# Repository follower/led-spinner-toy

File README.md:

# LED Spinner Toy

Flashy LED toy designed with KiCad

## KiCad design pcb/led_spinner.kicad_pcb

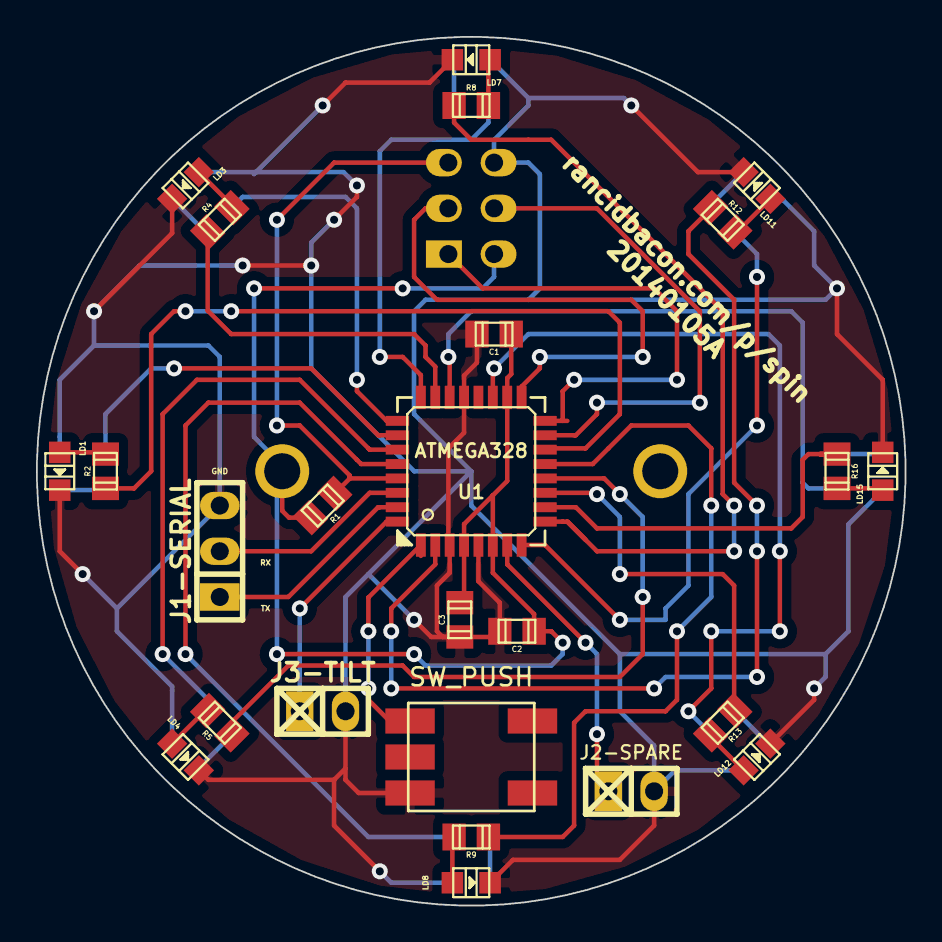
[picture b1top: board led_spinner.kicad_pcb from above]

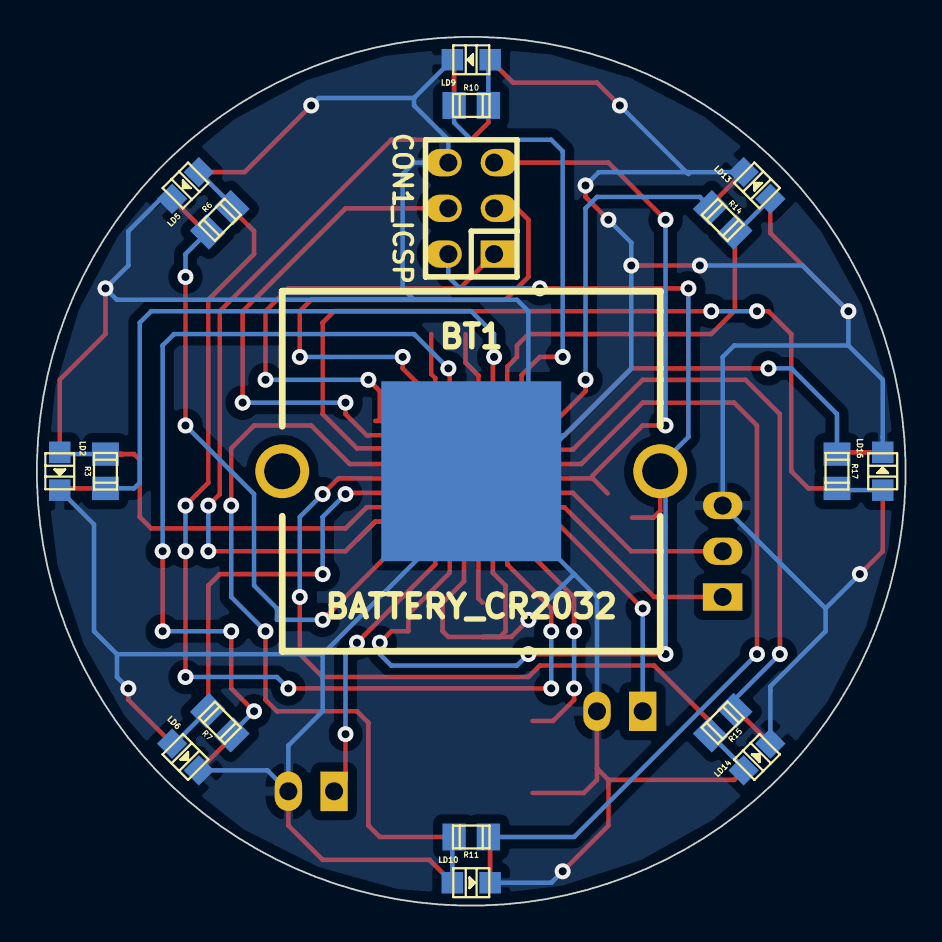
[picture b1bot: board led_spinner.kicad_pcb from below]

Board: 2 copper layers, 48.3 x 48.3 mm, 43 parts (18 on the bottom side), 43 nets.

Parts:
BT1: BATTERY_CR2032; CR2032_HOLDER_KEYSTONE_3003
C1, C2, C3: C; c_0805
CON1_ICSP: AVR-ISP-6; pin_socket_3x2
J1-SERIAL: SERIAL; pin_socket_3
J2-SPARE: SPARE; pin_socket_2
J3-TILT: TILT; pin_socket_2
LD1, LD2, LD3, LD4, LD5, LD6, LD7, LD8, LD9, LD10, LD11, LD12, LD13, LD14, LD15, LD16: LED; Led_0805
R1, R2, R3, R4, R5, R6, R7, R8, R9, R10, R11, R12, R13, R14, R15, R16, R17: R; r_0805
SW1: SW_PUSH; OMRON-PUSH-BUTTON-B3SN-3112P
U1: ATMEGA328; lqfp32

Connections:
+BATT: BT1.0, C1.2, C2.2, C3.1, CON1_ICSP.2, R1.1, U1.4, U1.6, U1.18
/BE: R17.2, U1.26
/BN: R10.2, U1.24
/BNE: R14.2, U1.25
/BNW: R6.2, U1.8
/BS: R11.2, U1.28
/BSE: R15.2, U1.27
/BSW: R7.2, U1.19
/BUTTON: SW1.1, U1.1
/BW: R3.2, U1.22
/FE: R16.2, U1.10
/FN: R8.2, U1.9
/FNE: R12.2, U1.2
/FNW: R4.2, U1.23
/FS: R9.2, U1.13
/FSE: R13.2, U1.11
/FSW: R5.2, U1.12
/FW: R2.2, U1.14
/MISO: CON1_ICSP.1, U1.16
/MOSI: CON1_ICSP.4, U1.15
/RXD: J1-SERIAL.2, U1.30
/SCK: CON1_ICSP.3, U1.17
/TXD: J1-SERIAL.1, U1.31
/~RESET: CON1_ICSP.5, R1.2, U1.29
GND: BT1.2, C1.1, C2.1, C3.2, CON1_ICSP.6, J1-SERIAL.3, J2-SPARE.2, J3-TILT.2, LD1.2, LD2.2, LD3.2, LD4.2, LD5.2, LD6.2, LD7.2, LD8.2, LD9.2, LD10.2, LD11.2, LD12.2, LD13.2, LD14.2, LD15.2, LD16.2, SW1.3, U1.3, U1.5, U1.21
unnamed: J2-SPARE.1, U1.7
unnamed: J3-TILT.1, U1.32
unnamed: LD1.1, R2.1
unnamed: LD2.1, R3.1
unnamed: LD3.1, R4.1
unnamed: LD4.1, R5.1
unnamed: LD5.1, R6.1
unnamed: LD6.1, R7.1
unnamed: LD7.1, R8.1
unnamed: LD8.1, R9.1
unnamed: LD9.1, R10.1
unnamed: LD10.1, R11.1
unnamed: LD11.1, R12.1
unnamed: LD12.1, R13.1
unnamed: LD13.1, R14.1
unnamed: LD14.1, R15.1
unnamed: LD15.1, R16.1
unnamed: LD16.1, R17.1

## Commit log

2013-12-22 Add default KiCad project file.
2013-12-22 Remove standard libraries.
2013-12-22 Import and include library <http://smisioto.no-ip.org/kicad_libs/library/lib_w_microcontrollers.zip> version (30/11/2013).
2013-12-22 Add default schematic file.
2013-12-24 Add ATmega328 to schematic.
2013-12-24 Move PCB related files into a subdirectory for better organisation.
2013-12-24 Add poor README.
2013-12-24 Import KiCad power library from <https://github.com/KiCad/kicad-library/raw/af0f01971809334bbfe6d6f22faec33e7056694c/library/power.lib>.
2013-12-24 Use KiCad power library.
2013-12-24 Add power flags required by KiCad.
2013-12-24 Move the MCU symbol so it's grid aligned.
2013-12-24 Add power and ground connections to MCU.
2013-12-24 Annotate the symbols.
2013-12-24 Import discrete device/components library from <http://smisioto.no-ip.org/kicad_libs/library/lib_w_device.zip> version (22/06/2013).
2013-12-24 Include previously imported library.
2013-12-24 Add imported library to schematic file also (not sure why this didn't happen before).
2013-12-24 Add decoupling caps.
2013-12-24 Add reset pull-up.
2013-12-24 Add TODO list to schematic.
2013-12-26 Import version of `atmel.lib` from <https://raw.github.com/KiCad/kicad-library/ed1b4733563014e8e1b31147cb90239def444825/library/atmel.lib> so we can use the AVR-ISP-6 schematic symbol. [Note: It's LG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
2013-12-26 Add imported library to project.
2013-12-26 Add ISP connector section.
2013-12-26 Add my CR2032 battery symbol (with the 3 pin workaround).
2013-12-26 Add CR2032 battery section to schematic.
2013-12-26 Add front & back side LEDs with appropriate PWM connections where required.
2013-12-26 Make AREF non-connected.
2013-12-26 Import and include connectors library from <http://smisioto.no-ip.org/kicad_libs/library/lib_w_connectors.zip> (version 12/10/2013).
2013-12-26 Add serial connector (not particularly standard).
2013-12-26 Add a connection point for a currently unused pin.
2013-12-26 Change the spare connection to have a ground connection too which probably makes it more useful--if we can fit it physically.
2013-12-26 Add connection point for tilt sensor.
2013-12-26 Rename unnamed connectors to indicate their use.
2013-12-26 Add the alternate pinout push button that I originally created for the reaction tester game project from the <http://smisioto.no-ip.org/> device library.
2013-12-26 Add button section.
2013-12-27 Add my custom footprints for push button switch and CR2032 battery retainer from reaction tester game repository.
2013-12-27 Import multiple footprints from <http://smisioto.no-ip.org/elettronica/kicad/kicad-en.htm>.
2013-12-27 Add generated net list.
2013-12-27 Remove default footprint library links.
2013-12-27 Remove alias thingy.
2013-12-27 Include libraries in project.
2013-12-27 KiCad automatic config change shenanigans.
2013-12-27 Add default component to footprint mapping file.
2013-12-27 Add "new style" library table with the libraries. Map components to footprints.
2013-12-27 Add default "blank" pcb layout.
2013-12-27 Add board outline to pcb. Add modules with rough (relative) positioning.
2013-12-27 Move four N,E,S,W front LEDs into correct place (based on current board size).
2013-12-27 Move all back side LEDs to the back of the board.
2013-12-27 Move front NE,SE,SW,NW LEDs into position. The positions aren't entirely perfect due to interaction between the 45 degree angle and the forced snap to grid.
2013-12-27 Fix LED/resistor pairs that didn't have the correct ends together.
2013-12-27 Add tracks between LED and resistors.
2013-12-27 Lay tracks to decoupling caps, reset pull up resistor and signal connections to all front LEDs.
2013-12-30 Route signals to back-side LEDs. Route signals to connectors except for ICSP. Route button.
2013-12-30 Remove some extra overlapping track segments.
2013-12-30 Route ICSP header. Route battery connections.
2013-12-30 Route ground connections in preparation for ground planes.
2013-12-30 Route one missed ground connection.
2013-12-30 Add ground zone on the front and back.
2013-12-30 Fix two DRC errors. The microcontroller pads are too close together according to the default rule so change the clearance for just that to 6 mil. There was one track too close to a SMD pad so fixed t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
2014-01-05 Tidy up the front silkscreen. (Remove off-board silkscreen. Remove overlaps. Add useful connector names.)
2014-01-05 Fix up back silkscreen.
2014-01-05 Add project and version ID text.
2014-01-05 Change PCB gerber export settings.
2014-01-05 Add exported Gerbers used to send to PCB manufacturer.
2014-11-05 Add the second initial revision of "half" of the enclosure.
2014-11-05 Add initial back part of enclosure. (Seems to be a little to thin to print well and also the inner edge isn't quite close enough to seal well.)
2014-11-05 Quick commit of sample code currently used for demo. Very power inefficient as it leaves "embers" behind on the LEDs.
2014-11-06 Revised version of back. Made thicker to print more reliably and adjusted inside to snuggly fit and hold in place.
2014-11-09 (Think) Added fillet to outside edge and reduced the height of the inset "shelf". Need to reduce overall height now too.
2014-11-10 Removed the temporary hole for the ISP connector as the new PCB doesn't have the connector permanently attached. Added a fillet ot the outside edge.
2014-11-10 Reduce height by 2mm because now that the "shelf" is lower we don't need as much height.
2014-11-10 Reduce the fillet curve slightly to match the top. Note: It turns out the new height is too short because I tested against the wrong point.
2014-11-10 Increase height by 1mm to get everything to fit. Which it now appears to do. :)
